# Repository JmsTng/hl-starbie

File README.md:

# My take on Starbie!
For week 1 of Hack Club Half Life, I followed the provided guide to build (and put my own spin on) Starbie. This version is designed with a space theme, with the silkscreen (graphics) and board shape based on Gargantua (the supermassive black hole in Interstellar).<br>
This current version uses a DS3231 Real-Time Clock (RTC) module to keep track of time, and a MPU6050 accelerometer. Combined, these sensors are theoretically (but not practically) enough to correct for relativistic time dilation.

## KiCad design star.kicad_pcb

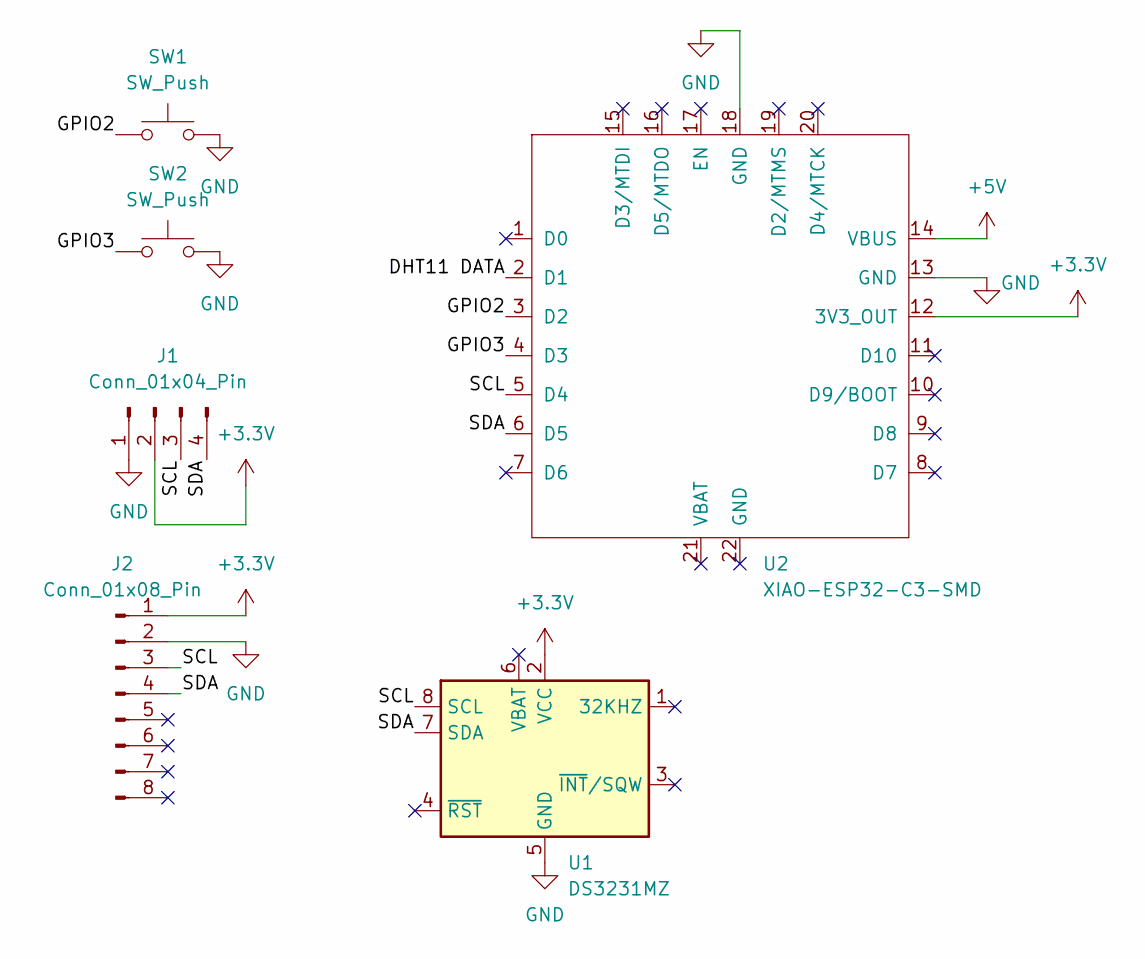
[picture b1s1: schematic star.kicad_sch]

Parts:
J1: Conn_01x04_Pin; Display_128x64_096_I2C
J2: Conn_01x08_Pin; PinHeader_1x08_P2.54mm_Vertical
SW1, SW2: SW_Push; SW_Cherry_MX_1.00u_PCB
U1: DS3231MZ; SOIC-8_3.9x4.9mm_P1.27mm
U2: XIAO-ESP32-C3-SMD

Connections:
+3.3V: J1.2, J2.1, U1.2 (VCC), U2.12 (3V3_OUT)
+5V: U2.14 (VBUS)
/DHT11 DATA: U2.2 (D1)
/GPIO2: SW1.1, U2.3 (D2)
/GPIO3: SW2.1, U2.4 (D3)
/SCL: J1.3, J2.3, U1.8 (SCL), U2.5 (D4)
/SDA: J1.4, J2.4, U1.7 (SDA), U2.6 (D5)
GND: J1.1, J2.2, SW1.2, SW2.2, U1.5 (GND), U2.13 (GND), U2.18 (GND)

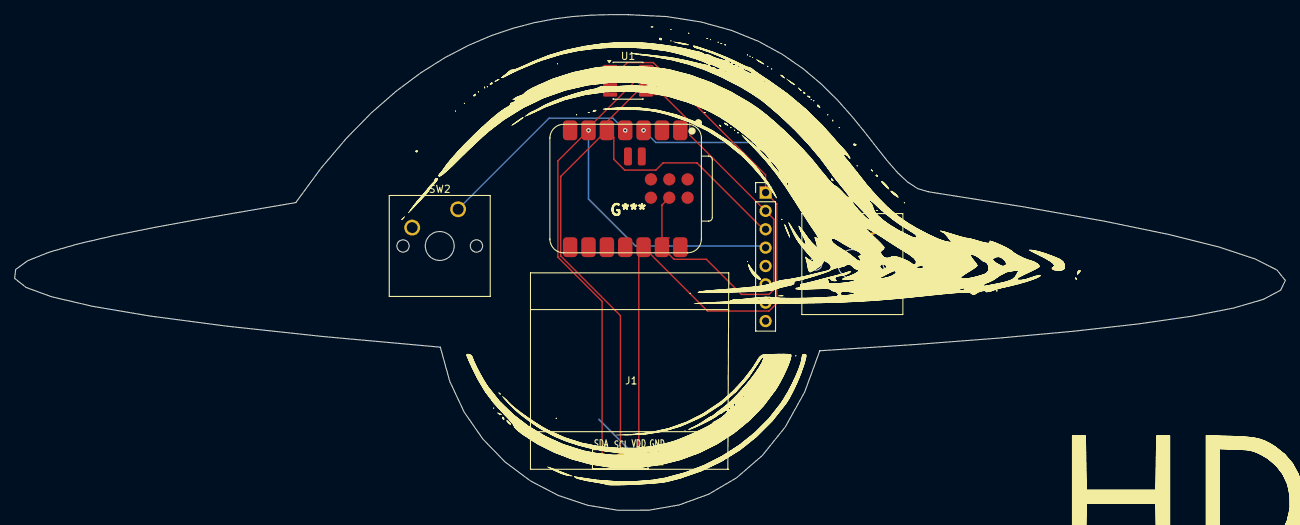
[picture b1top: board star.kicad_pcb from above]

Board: 2 copper layers, 175.8 x 68.6 mm, 6 parts (0 on the bottom side), 6 nets.
